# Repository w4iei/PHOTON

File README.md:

# PHOTON
**PHysical Optical Tracking of Notes system**

PHOTON is a modular, open-source optical sensing platform for high-resolution key and motion tracking. Each module combines a KiCad-designed linear array of **VCNT2025X01** reflective sensors, **TLA2518** high-speed SPI ADCs, and an **RP2350** MCU. Modules can run standalone over USB-C or daisy-chain over RS-485 for large sensing surfaces.

## Paper
[PHOTON: Non-Invasive Optical Tracking of Key-Lever Motion in Historical Keyboard Instruments](https://arxiv.org/abs/2604.21682) (arXiv:2604.21682)

## Demo

[Watch the PHOTON demo playlist on YouTube](https://www.youtube.com/playlist?list=PLzCRAfVYuoWGEnWNO6l8IuFvaSUI3v1Gd)

## Highlights
- **Sensors:** [VCNT2025X01](https://www.vishay.com/en/product/84895/) reflective array with per-sensor enable lines
- **Digitization:** [TLA2518](https://www.ti.com/product/TLA2518) SPI ADCs for high-speed readout
- **MCU:** [RP2350](https://www.raspberrypi.com/products/rp2350/) (dual-core Cortex-M33)
- **Comms:** [THVD1424](https://www.ti.com/product/THVD1424) RS-485 transceivers; firmware-controlled termination on the main board (idle-bus failsafe via the transceiver's internal receiver thresholds on this hardware rev)
- **I/O:** USB-C (power + USB-MIDI/CDC), QWIIC/I2C expansion
- **Black box:** a microSD card in the bridge records every performance as Standard MIDI Files, host or no host (see [firmware/README.md](firmware/README.md#microsd-recorder-bridge))
- **Open:** KiCad 9 hardware, native C firmware (Pico SDK)

## Performance
- Full 31-sensor board sweep in ~770 µs — ~1.3 kHz open-loop; production runs two-phase, pace-throttled at 600 Hz (half the peak emitter current, 1.67 ms velocity quantisation) with µs-resolution velocity timing either way
- RS-485 bus at 4 Mbaud, bridge-polled: zero collisions by construction, zero event loss across ~500k sequence-accounted bench events, sub-ms worst-case event latency with four boards on the bus

## Firmware (native C, dual-core)
CircuitPython support is gone: it capped the system at a ~250 Hz single-core scan loop and could not prevent bus collisions, so it was retired for performance. The native Pico-SDK firmware ships as **one UF2 for every board** — each board probes its own hardware at boot and becomes a sensor node or the main bridge automatically:
- **Core 1** owns the sensor array: pipelined TLA2518 scanning, running entirely from SRAM so flash and USB activity can never stall a sweep.
- **Core 0** owns everything else: USB (CDC console + USB-MIDI), the RS-485 protocol, calibration and configuration storage.
- **RS-485:** one board is the sole bus master — the main board, or with `master on` the sensor board that carries the USB cable — and polls each sensor board in turn; nodes never transmit unsolicited, and every event batch is acknowledged before a node releases it — collision-free and lossless by design.
- **Scanning:** free-runs open-loop at ~1.3 kHz; throttled to a paced 600 Hz (two-phase mode) for production use.
- **microSD recorder:** a card in the bridge records every performance automatically as Standard MIDI Files, numbered per power-on and per playing episode, with no host, no setup and no clock required.

Build and flash instructions: `firmware/README.md`.

## Architecture (Short)
- Sensor boards: VCNT2025X01 array -> TLA2518 SPI ADCs -> RP2350
- Main board: RP2350 + THVD1424 RS-485 + bias resistors + termination control
- Bus: RS-485 differential, terminated at endpoints

## Hardware
See `hardware/README.md` for board-specific notes and layout sources.

## Getting Started
**Hardware**
- PHOTON module(s)
- USB-C cable
- JST-SH 4-pin cables (1.0 mm pitch, "reverse double head" type as used by Qwiic; see `hardware/README.md`)
- Mounting screws: **M2.3 x 5 mm pan head**, through the boards' 2.7 mm (M2.5) holes; at least three per board over 250 mm long, one at each end and one near the middle (see [hardware/README.md](hardware/README.md#design-recommendations))

**Software**
- PHOTON firmware UF2 (build from `firmware/`, see `firmware/README.md`)
- KiCad 9 (download: https://www.kicad.org/download/)
- DAW or MIDI viewer (Pianoteq, Ableton Live, Reaper, Max/MSP, etc.)

## Build & Flash
1. A new board arrives with empty flash, so it comes up in BOOTSEL on its own: connect via USB-C and copy `photon.uf2` to the mounted `RP2350` drive. The same image runs every board.
2. On each sensor board, set its bus id once via the USB console (`setid N`); in an instrument without a main board, also `master on` on each (see `firmware/README.md`).
3. Calibrate. Two ways:
   - **One board, on its own USB console:** `r` clears that board's table and starts learning; play every key it covers once, one at a time, with a normal full stroke; `s` freezes the table and saves it (`x` aborts without saving).
   - **The whole instrument, from the bridge console:** `cal reset` clears every sensor board and starts learning on all of them; play every key on every manual; `cal save` then stores each board's table in its own flash. To redo a single board without disturbing the others, give its bus id: `cal reset <id>`, play that board's keys, `cal save <id>`.

   Calibration and configuration persist in flash and survive reflashing; only `cal reset`, `r` and `setid` clear them.
4. Boards already running PHOTON reflash over USB alone: the `bootsel` console command re-enters the bootloader, so the `RP2350` drive comes back without touching the board. **USB-BOOT** (hold while connecting USB-C, or short the jumper) is only needed to recover a board whose console is unreachable.

## Notes
- **Double-manual harpsichords** run on a single bus: each manual is a pair of sensor boards mapped to its own MIDI channel (`chmap` console command). The polled protocol eliminates inter-board collisions, so simultaneous playing on both manuals loses nothing.

## Citation
```bibtex
@inproceedings{photon2026,
  title       = {PHOTON: Non-Invasive Optical Tracking of Key-Lever Motion in Historical Keyboard Instruments},
  author      = {Noah Jaffe and John Ashley Burgoyne},
  booktitle   = {Proceedings of the 2026 International Conference on New Interfaces for Musical Expression (NIME)},
  year        = {2026},
  address     = {London, UK},
  note        = {23--26 June 2026. Preprint: arXiv:2604.21682},
  url         = {https://arxiv.org/abs/2604.21682},
}
```

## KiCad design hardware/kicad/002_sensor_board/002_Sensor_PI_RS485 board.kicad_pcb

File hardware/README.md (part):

## Hardware Overview

KiCad sources for the PHOTON boards. Three designs, all sharing one symbol
library (`PHOTON.kicad_sym`, `PHOTON_Modified.kicad_sym`) and one footprint
library (`photon_common.pretty`) at the top of `hardware/kicad/`.

| Board | Size | Role |
|---|---|---|
| `002_sensor_board` | 413.7 x 35.0 mm | Sensor node — 31 optical sensors |
| `001d_..._low_profile` | 54.0 x 41.7 mm | Bridge, low cost / low profile |
| `001_main_controller_board` | 69.0 x 49.9 mm | Bridge, full size, touchscreen |

### Datasheets

- [VCNT2025X01](https://www.vishay.com/docs/84895/vcnt2025x01.pdf) — reflective optical sensor (Vishay)
- [TLA2518](https://www.ti.com/lit/ds/symlink/tla2518.pdf) — 8-channel SPI ADC (TI)
- [RP2350 / RP2354](https://datasheets.raspberrypi.com/rp2350/rp2350-datasheet.pdf) — microcontroller (Raspberry Pi); the RP2354 is the RP2350 with 2 MB of flash in the package, same datasheet
- [THVD1424](https://www.ti.com/lit/ds/symlink/thvd1424.pdf) — RS-485 transceiver (TI)
- [TPS62A0569A](https://www.ti.com/lit/gpn/tps62a0569a) — buck regulator (TI)
- [Waveshare 2.8" capacitive touch LCD](https://www.waveshare.com/wiki/2.8inch_Capacitive_Touch_LCD) — ST7789T3 display controller, CST328 touch controller; the reference panel for the 001 bridge

## 002 — Sensor node

31 VCNT2025X01 reflective sensors on a **13.3 mm pitch**, read by eight
TLA2518 8-channel ADCs, scanned by an RP2354. One board covers 31 notes, so
**two boards cover a 56-62 key manual** and four cover a double-manual
instrument.

This example is dimensioned for 13.3 mm, measured at either sensing point —
under the **jack** or under the **key lever**. **Every harpsichord is
different.** Measure your own instrument and validate the fit before ordering
boards.

Smaller compasses (58 keys GG–e‴, for example) often have no centre vertical
rail, so the boards mount on the horizontal rail near the pins at the far end
of the keybed; check the clearance there carefully. Many instruments taper,
so the jack spacing is not 13.33 mm: either make a board to match, or mount
the standard board where the keys' centre-to-centre spacing is 13.33 mm.

**The board is designed to be shortened.** Mousebite perforations
(`photon_common:mousebite_34mm`) let you snap or cut sections off with
scissors to fit a shorter compass or an awkward case. Signals are routed
*through* the mousebite regions — sensor enables, ADC inputs, VCC and GND —
so a cut section stays functional up to the break.

## 001D — Bridge, low profile

RP2354 (2 MB internal flash), USB-C to the host, THVD1424 to the sensor bus,
microSD. Minimal part count and the smallest board that does the job. This is
the default bridge.

## 001 — Bridge, full size

Same role, plus an **18-pin 0.5 mm FPC connector (FH34SRJ-18S-0.5SH)** for a
touchscreen — the reference panel is a Waveshare 2.8" 240x320, ST7789T3 over
SPI with a CST328 capacitive touch controller over I2C. Carries RP2350 with
external W25Q128 flash and an APS6404L PSRAM, plus one VCNT2025X01 fitted for
bench work. Use this only if the application wants a local display.

### Touchscreen and PSRAM bring-up notes

Verified on 2026-09-30 on an early 001 ("A003"). Its pins match every
schematic revision:

| Signal | GPIO |
|---|---|
| LCD SPI1 SCK / MOSI / MISO | 10 / 11 / 12 (shared with the microSD socket) |
| LCD CS / DC / RST / backlight | 8 / 14 / 9 / 15 |
| Touch I2C1 SDA / SCL | 6 / 7 |
| Touch INT / RST | 2 / 3 |
| PSRAM CS (QMI CS1) | 0 |

- **Display.** The ST7789T3 runs at 37.5 MHz SPI (clk_peri / 4), with colour
  order RGB and inversion on. It **never answers register reads** on this
  board: MISO and SDA both read the microSD socket's pull-ups. So check first
  light by eye, not by reading an ID.
- **Touch.** The CST328 (address 0x1A, signature 0xCACA, reports 240x320)
  sends a report every ~26 ms while a finger is down. **INT falls about 2 ms
  before the report registers are updated.** Read the chip right on the edge
  and you get the previous, already-consumed report, which says zero
  fingers. So wait ~2 ms after INT, and treat a finger as lifted only after
  ~80 ms without a report. The observed worst gap was 72 ms. A shorter window
  releases and re-presses a held finger, and that double-toggles buttons.
- **PSRAM.** The APS6404L answers on GPIO0 (known-good-die byte 0x5D, 8 MB). A full
  8 MB write/read test passed with 0 errors.

Firmware support lives in `firmware/src/hw/psram.c` (board support; the
PHOTON image doesn't call it). The **optional** touchscreen drivers are in
`firmware/src/touchscreen/`. They are only for firmware that wants a local
UI, and are built only with `-DPHOTON_TOUCHSCREEN=ON`, which fetches LVGL.

## No bridge at all

**Neither bridge board is required.** A sensor node has its own USB-C
receptacle, so running a USB-C cable from one sensor board straight to the
host is a complete system. Several sensor boards work the same way once each
has `master on` saved: the board carrying the USB cable runs the bus for the
others (see
[firmware/README.md](../firmware/README.md#without-a-main-controller-board)).
The bridge exists for installations that want the host connection somewhere
other than at a sensor board, or that want a touchscreen and the microSD
recorder.

In practice a bridge is often the easier build. Once the sensor boards are
mounted under the keys or jacks, their USB-C receptacles tend to end up
somewhere a USB-C plug cannot reach or cannot exit the case from. The
inter-board lead is a thin 4-pin JST-SH cable that bends around anything, so
the bridge — and with it the USB-C socket and the microSD slot — can sit
wherever the host connection is convenient. The cable type is specified under
[Power](#power).

## Power

**The RS-485 cable carries 5 V.** Every board — sensor node and bridge alike —
regulates its own 3.3 V locally with a TPS62A0569ADRLR buck. Nets are just
`+5V` and `+3V3`; there is no shared 3.3 V rail between boards.

Inter-board cable, 4-pin JST-SH:

| Pin | Net |
|---|---|
| 1 | GND |
| 2 | +5V |
| 3 | RS485_P |
| 4 | RS485_N |

Use a 4-pin JST-SH (1.0 mm pitch) **"reverse double head"** cable — the same
lead Qwiic uses. Check it before plugging in: hold both plugs facing you in
the same orientation and the top-left wire colour must be the same on both.
[Example listing](https://nl.aliexpress.com/item/1005011775162638.html).

Feedback divider is 0.6 V x (1 + 450k/100k) = 3.3 V.

### One host at a time

Every board's USB-C VBUS sits on the same `+5V` net as its RS-485 connectors,
so the whole chain shares one 5 V rail. Powering any single board over USB
powers every board on the bus — which is what makes an instrument without a
main controller board work (`master on` on every sensor board; the one with
the USB cable runs the bus, see
[firmware/README.md](../firmware/README.md#without-a-main-controller-board)).

**Do not plug two boards into two different computers at once.** That ties both
hosts' 5 V supplies together through the cable. One USB connection to the
system at a time.

### Budget

The whole four-board system draws **~210 mA at 5 V (1.08 W)** while
scanning at the production settings, i.e. roughly 60 mA at 3.3 V per board:
the RP2350 at 150 MHz and eight always-on TLA2518s. Emitters are pulsed at a
few percent duty and cost ~0.1 W per 100 Hz of scan rate; peak current
depends on scan mode (up to four lit at once in two-phase, ~27 mA each, or
eight in parallel).

COUT is **22 uF**, the value the TPS62A0569A datasheet rates highest with a
1 uH inductor. Do not add distributed bulk on +3V3 to "help" — it parallels
COUT and slows the loop, which costs more than the droop it removes.

### Rail sensitivity

The detector is a 4.7 kOhm pull-up to +3V3 with the ADC referenced to the same
rail, so the dark reading is ratiometric and only the LED's forward-voltage
offset leaks through: **~1.9% of signal per 100 mV of droop**, about 130 counts
on a 6,900-count range against a ~62-count noise floor. Keep emitter-correlated
droop under ~50 mV and it is invisible.

Do not filter AVDD away from the pull-up rail — that breaks the cancellation
and roughly triples the sensitivity.

## Building a sensor board for your instrument

1. Update the schematic so the sensor and bank counts match your instrument.
   The final sensor bank is **not** inherited from the four-sensor bank — edit
   it explicitly.
2. Resize the board outline, copper fills and edge cuts.
3. Run the sensor placement script to set the pitch.
4. Route the first bank and the last bank.
5. Replicate that routing across the middle banks, then clean up and verify by
   hand.

Manual review is required after replication and before fabrication.

## Required KiCad plugins

Both via the Plugin and Content Manager:

- **Replicate Layout** — step 5 above
- **Fabrication Toolkit** — generates the `production/` outputs

## Design recommendations

For a board over 250 mm long, use at least **three M2.5 mounting holes** — one at each
end and one near the middle. The centre screw stops the board bowing away from
the mounting surface. Fit them in a line, not both ends first. Putty is fine
for a temporary setup; screws keep the boards from shifting when the
instrument is moved.

Mounting holes use `photon_common:MountingHole_2.7mm_M2.5_Keepout`, which
carries a 7 mm copper keepout so a screw head cannot bridge the top pour to
the bottom pour.

Recommended screws: **M2.3 x 5 mm pan head**
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
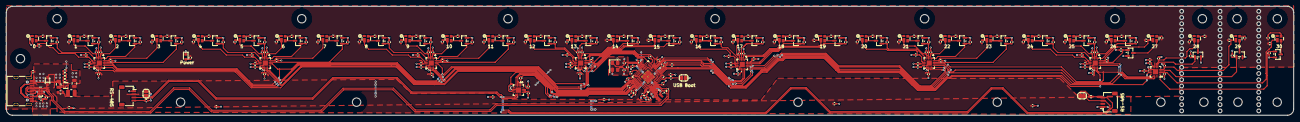
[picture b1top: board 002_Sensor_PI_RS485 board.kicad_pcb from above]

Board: 2 copper layers, 413.7 x 35.0 mm, 300 parts (0 on the bottom side), 183 nets.

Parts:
C1: 4.7uF; C_0805_2012Metric
C2, C3: 4.7uF; C_0402_1005Metric_small_pads
C4: 22uF; C_0805_2012Metric
C5, C8, C9, C13, C14, C15, C16, C19, C20, C21, C22, C23, C24, C25, C26, C27: 100nF; C_0402_1005Metric
C6, C7: 4.7uF; C_0402_1005Metric
C10, C401, C402, C403, C801, C802, C803, C1301, C1302, C1303, C1801, C1802, C1803, C2301, C2302, C2303, C2801, C2802, C2803, C3301, C3302, C3303, C3801, C3802, C3803: 1uF; C_0402_1005Metric
C17, C18: 15pF; C_0402_1005Metric
C404, C405, C406, C407, C804, C805, C806, C807, C1304, C1305, C1306, C1307, C1804, C1805, C1806, C1807, C2304, C2305, C2306, C2307, C2804, C2805, C2806, C2807, C3304, C3305, C3306, C3307, C3804, C3805, C3806: 1nF; C_0402_1005Metric
CR1: PTVSHC3D7VU; SOD-323_L1.8-W1.3-LS2.5-RD
D3: LED RED; LED_0603_1608Metric
FB1: FerriteBead; L_0603_1608Metric
H1, H2, H3, H4, H5, H6, H7, H8, H9, H10, H11, H12, H13, H14, H15, H16, H17, H18: MountingHole; MountingHole_2.7mm_M2.5_Keepout
H3801, H3802, H3803: Mousebites to detatch sensor; mousebite_34mm
J1, J2: JST_SH; JST_SH_SM04B-SRSS-TB_1x04-1MP_P1.00mm_Horizontal
J3: USB_C_Receptacle_USB2.0; USB_C_Receptacle_HRO_TYPE-C-31-M-12
JP1, JP2, JP4: SolderJumper_2_Open; SolderJumper-2_P1.3mm_Open_RoundedPad1.0x1.5mm
L1: 3.3uH; L_pol_2016
L2: 1uH; L_1008_2520Metric
Q301, Q501, Q601, Q701, Q901, Q1001, Q1101, Q1201, Q1401, Q1501, Q1601, Q1701, Q1901, Q2001, Q2101, Q2201, Q2401, Q2501, Q2601, Q2701, Q2901, Q3001, Q3101, Q3201, Q3401, Q3501, Q3601, Q3701, Q4301, Q4401, Q4501: AO3400A; SOT-23
R1: 0Ω; R_0402_1005Metric
R2, R3: 5.1kΩ; R_0402_1005Metric
R4, R5: 120Ω; R_0402_1005Metric
R6, R11, R12: 33Ω; R_0402_1005Metric
R7, R18: 1kΩ; R_0402_1005Metric
R8, R102: 10kΩ; R_0402_1005Metric
R13, R14, R19, R20: 22Ω; R_0402_1005Metric
R103, R301, R501, R601, R701, R901, R1001, R1101, R1201, R1401, R1501, R1601, R1701, R1901, R2001, R2101, R2201, R2401, R2501, R2601, R2701, R2901, R3001, R3101, R3201, R3401, R3501, R3601, R3701, R4301, R4401, R4501: 100kΩ; R_0402_1005Metric
R104, R105: 200kΩ; R_0402_1005Metric
R106: 51kΩ; R_0402_1005Metric
R302, R502, R602, R702, R902, R1002, R1102, R1202, R1402, R1502, R1602, R1702, R1902, R2002, R2102, R2202, R2402, R2502, R2602, R2702, R2902, R3002, R3102, R3202, R3402, R3502, R3602, R3702, R4302, R4402, R4502: 68Ω; R_0402_1005Metric
R303, R503, R603, R703, R903, R1003, R1103, R1203, R1403, R1503, R1603, R1703, R1903, R2003, R2103, R2203, R2403, R2503, R2603, R2703, R2903, R3003, R3103, R3203, R3403, R3503, R3603, R3703, R4303, R4403, R4503: 4.7kΩ; R_0402_1005Metric
U1: RP2354_60QFN; RP2350-QFN-60-1EP_7x7_P0.4mm_EP3.4x3.4mm_ThermalVias
U4: TPD4E05U06DQAR; DQA0010A
U5: THVD1424RGTR; QFN_24RGTR_TEX
U6: TPS62A0569ADRLR; SOT-563_DRL0006A
U301, U501, U601, U701, U901, U1001, U1101, U1201, U1401, U1501, U1601, U1701, U1901, U2001, U2101, U2201, U2401, U2501, U2601, U2701, U2901, U3001, U3101, U3201, U3401, U3501, U3601, U3701, U4301, U4401, U4501: VCNT2025X01; VCNT2025X01_VIS
U401, U801, U1301, U1801, U2301, U2801, U3301, U3801: TLA2518IRTER; WQFN16_RTE_TEX
Y1: ABM8-272-T3; Crystal_SMD_3225-4Pin_3.2x2.5mm

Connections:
+1V1: C3.1, C5.1, C7.1, C8.1, L1.1, U1.6 (DVDD), U1.23 (DVDD), U1.39 (DVDD), U1.50 (VREG_FB)
+3V3: C2.1, C4.1, C9.1, C10.1, C13.1, C14.1, C15.1, C16.1, C19.1, C20.1, C21.1, C401.1, C403.1, C801.1, C803.1, C1301.1, C1303.1, C1801.1, C1803.1, C2301.1, C2303.1, C2801.1, C2803.1, C3301.1, C3303.1, C3801.1, C3803.1, L2.2, R6.1, R8.2, R102.2, R104.2, R302.1, R303.1, R502.1, R503.1, R602.1, R603.1, R702.1, R703.1, R902.1, R903.1, R1002.1, R1003.1, R1102.1, R1103.1, R1202.1, R1203.1, R1402.1, R1403.1, R1502.1, R1503.1, R1602.1, R1603.1, R1702.1, R1703.1, R1902.1, R1903.1, R2002.1, R2003.1, R2102.1, R2103.1, R2202.1, R2203.1, R2402.1, R2403.1, R2502.1, R2503.1, R2602.1, R2603.1, R2702.1, R2703.1, R2902.1, R2903.1, R3002.1, R3003.1, R3102.1, R3103.1, R3202.1, R3203.1, R3402.1, R3403.1, R3502.1, R3503.1, R3602.1, R3603.1, R3702.1, R3703.1, R4302.1, R4303.1, R4402.1, R4403.1, R4502.1, R4503.1, U1.1 (IOVDD), U1.11 (IOVDD), U1.20 (IOVDD), U1.30 (IOVDD), U1.38 (IOVDD), U1.44 (ADC_AVDD), U1.45 (IOVDD), U1.49 (VREG_VIN), U1.53 (USB_OTP_VDD), U1.54 (QSPI_IOVDD), U5.13 (VIO), U5.14 (VCC), U5.15 (H/F), U401.7 (AVDD), U401.10 (DVDD), U801.7 (AVDD), U801.10 (DVDD), U1301.7 (AVDD), U1301.10 (DVDD), U1801.7 (AVDD), U1801.10 (DVDD), U2301.7 (AVDD), U2301.10 (DVDD), U2801.7 (AVDD), U2801.10 (DVDD), U3301.7 (AVDD), U3301.10 (DVDD), U3801.7 (AVDD), U3801.10 (DVDD)
+5V: C22.1, C23.1, C24.1, C25.1, C26.1, C27.1, CR1.1 (K), FB1.1, J1.2, J2.2, J3.A4 (VBUS), J3.A9 (VBUS), J3.B4 (VBUS), J3.B9 (VBUS)
/BANK_0_CS: U1.33 (GPIO21), U401.11 (*CS)
/BANK_1_CS: U1.32 (GPIO20), U801.11 (*CS)
/BANK_2_CS: U1.31 (GPIO19), U1301.11 (*CS)
/BANK_3_CS: U1.19 (GPIO15), U1801.11 (*CS)
/BANK_4_CS: U1.3 (GPIO1), U2301.11 (*CS)
/BANK_5_CS: U1.10 (GPIO7), U2801.11 (*CS)
/BANK_6_CS: U1.8 (GPIO5), U3301.11 (*CS)
/BANK_7_CS: U1.9 (GPIO6), U3801.11 (*CS)
/GPIO0: U1.2 (GPIO0), U2301.12 (SDO), U2801.12 (SDO), U3301.12 (SDO), U3801.12 (SDO)
/GPIO2: R14.2, U1.4 (GPIO2)
/GPIO3: U1.5 (GPIO3), U2301.14 (SDI), U2801.14 (SDI), U3301.14 (SDI), U3801.14 (SDI)
/GPIO8: U1.12 (GPIO8), U401.12 (SDO), U801.12 (SDO), U1301.12 (SDO), U1801.12 (SDO)
/GPIO10: R13.2, U1.14 (GPIO10)
/GPIO11: U1.15 (GPIO11), U401.14 (SDI), U801.14 (SDI), U1301.14 (SDI), U1801.14 (SDI)
/GPIO22: R19.2, U1.34 (GPIO22)
/GPIO23: R20.2, U1.35 (GPIO23)
/GPIO24: U1.36 (GPIO24), U5.2 (RE), U5.3 (DE)
/GPIO25: U1.37 (GPIO25), U5.5 (TERM_TX), U5.7 (TERM_RX)
/QSPI_SS: R7.1, U1.60 (QSPI_SS)
/RS485_N: J1.4, J2.4, R4.2, R5.2, U5.10 (Z)
/RS485_P: J1.3, J2.3, JP1.1 (A), JP2.1 (A), U5.9 (Y)
/RUN: R102.1, U1.26 (RUN)
/SPI0_SCLK: R13.1, U401.13 (SCLK), U801.13 (SCLK), U1301.13 (SCLK), U1801.13 (SCLK)
/SPI1_SCLK: R14.1, U2301.13 (SCLK), U2801.13 (SCLK), U3301.13 (SCLK), U3801.13 (SCLK)
/Sensor Array/4_Sensor_bank1/EN0: Q901.1 (G), R901.1, U801.5 (AIN6/GPIO6)
/Sensor Array/4_Sensor_bank1/EN1: Q1001.1 (G), R1001.1, U801.3 (AIN4/GPIO4)
/Sensor Array/4_Sensor_bank1/EN2: Q1101.1 (G), R1101.1, U801.1 (AIN2/GPIO2)
/Sensor Array/4_Sensor_bank1/EN3: Q1201.1 (G), R1201.1, U801.15 (AIN0/GPIO0)
/Sensor Array/4_Sensor_bank1/Y0: C804.1, R903.2, U801.6 (AIN7/GPIO7), U901.2
/Sensor Array/4_Sensor_bank1/Y1: C805.1, R1003.2, U801.4 (AIN5/GPIO5), U1001.2
/Sensor Array/4_Sensor_bank1/Y2: C806.1, R1103.2, U801.2 (AIN3/GPIO3), U1101.2
/Sensor Array/4_Sensor_bank1/Y3: C807.1, R1203.2, U801.16 (AIN1/GPIO1), U1201.2
/Sensor Array/4_Sensor_bank2/EN0: Q1401.1 (G), R1401.1, U1301.5 (AIN6/GPIO6)
/Sensor Array/4_Sensor_bank2/EN1: Q1501.1 (G), R1501.1, U1301.3 (AIN4/GPIO4)
/Sensor Array/4_Sensor_bank2/EN2: Q1601.1 (G), R1601.1, U1301.1 (AIN2/GPIO2)
/Sensor Array/4_Sensor_bank2/EN3: Q1701.1 (G), R1701.1, U1301.15 (AIN0/GPIO0)
/Sensor Array/4_Sensor_bank2/Y0: C1304.1, R1403.2, U1301.6 (AIN7/GPIO7), U1401.2
/Sensor Array/4_Sensor_bank2/Y1: C1305.1, R1503.2, U1301.4 (AIN5/GPIO5), U1501.2
/Sensor Array/4_Sensor_bank2/Y2: C1306.1, R1603.2, U1301.2 (AIN3/GPIO3), U1601.2
/Sensor Array/4_Sensor_bank2/Y3: C1307.1, R1703.2, U1301.16 (AIN1/GPIO1), U1701.2
/Sensor Array/4_Sensor_bank3/EN0: Q1901.1 (G), R1901.1, U1801.5 (AIN6/GPIO6)
/Sensor Array/4_Sensor_bank3/EN1: Q2001.1 (G), R2001.1, U1801.3 (AIN4/GPIO4)
/Sensor Array/4_Sensor_bank3/EN2: Q2101.1 (G), R2101.1, U1801.1 (AIN2/GPIO2)
/Sensor Array/4_Sensor_bank3/EN3: Q2201.1 (G), R2201.1, U1801.15 (AIN0/GPIO0)
/Sensor Array/4_Sensor_bank3/Y0: C1804.1, R1903.2, U1801.6 (AIN7/GPIO7), U1901.2
/Sensor Array/4_Sensor_bank3/Y1: C1805.1, R2003.2, U1801.4 (AIN5/GPIO5), U2001.2
/Sensor Array/4_Sensor_bank3/Y2: C1806.1, R2103.2, U1801.2 (AIN3/GPIO3), U2101.2
/Sensor Array/4_Sensor_bank3/Y3: C1807.1, R2203.2, U1801.16 (AIN1/GPIO1), U2201.2
/Sensor Array/4_Sensor_bank4/EN0: Q2401.1 (G), R2401.1, U2301.5 (AIN6/GPIO6)
/Sensor Array/4_Sensor_bank4/EN1: Q2501.1 (G), R2501.1, U2301.3 (AIN4/GPIO4)
/Sensor Array/4_Sensor_bank4/EN2: Q2601.1 (G), R2601.1, U2301.1 (AIN2/GPIO2)
/Sensor Array/4_Sensor_bank4/EN3: Q2701.1 (G), R2701.1, U2301.15 (AIN0/GPIO0)
/Sensor Array/4_Sensor_bank4/Y0: C2304.1, R2403.2, U2301.6 (AIN7/GPIO7), U2401.2
/Sensor Array/4_Sensor_bank4/Y1: C2305.1, R2503.2, U2301.4 (AIN5/GPIO5), U2501.2
/Sensor Array/4_Sensor_bank4/Y2: C2306.1, R2603.2, U2301.2 (AIN3/GPIO3), U2601.2
/Sensor Array/4_Sensor_bank4/Y3: C2307.1, R2703.2, U2301.16 (AIN1/GPIO1), U2701.2
/Sensor Array/4_Sensor_bank5/EN0: Q2901.1 (G), R2901.1, U2801.5 (AIN6/GPIO6)
/Sensor Array/4_Sensor_bank5/EN1: Q3001.1 (G), R3001.1, U2801.3 (AIN4/GPIO4)
/Sensor Array/4_Sensor_bank5/EN2: Q3101.1 (G), R3101.1, U2801.1 (AIN2/GPIO2)
/Sensor Array/4_Sensor_bank5/EN3: Q3201.1 (G), R3201.1, U2801.15 (AIN0/GPIO0)
/Sensor Array/4_Sensor_bank5/Y0: C2804.1, R2903.2, U2801.6 (AIN7/GPIO7), U2901.2
/Sensor Array/4_Sensor_bank5/Y1: C2805.1, R3003.2, U2801.4 (AIN5/GPIO5), U3001.2
/Sensor Array/4_Sensor_bank5/Y2: C2806.1, R3103.2, U2801.2 (AIN3/GPIO3), U3101.2
/Sensor Array/4_Sensor_bank5/Y3: C2807.1, R3203.2, U2801.16 (AIN1/GPIO1), U3201.2
/Sensor Array/4_Sensor_bank6/EN0: Q3401.1 (G), R3401.1, U3301.5 (AIN6/GPIO6)
/Sensor Array/4_Sensor_bank6/EN1: Q3501.1 (G), R3501.1, U3301.3 (AIN4/GPIO4)
/Sensor Array/4_Sensor_bank6/EN2: Q3601.1 (G), R3601.1, U3301.1 (AIN2/GPIO2)
/Sensor Array/4_Sensor_bank6/EN3: Q3701.1 (G), R3701.1, U3301.15 (AIN0/GPIO0)
/Sensor Array/4_Sensor_bank6/Y0: C3304.1, R3403.2, U3301.6 (AIN7/GPIO7), U3401.2
/Sensor Array/4_Sensor_bank6/Y1: C3305.1, R3503.2, U3301.4 (AIN5/GPIO5), U3501.2
/Sensor Array/4_Sensor_bank6/Y2: C3306.1, R3603.2, U3301.2 (AIN3/GPIO3), U3601.2
/Sensor Array/4_Sensor_bank6/Y3: C3307.1, R3703.2, U3301.16 (AIN1/GPIO1), U3701.2
/Sensor Array/4_Sensor_bank/EN0: Q301.1 (G), R301.1, U401.5 (AIN6/GPIO6)
/Sensor Array/4_Sensor_bank/EN1: Q501.1 (G), R501.1, U401.3 (AIN4/GPIO4)
/Sensor Array/4_Sensor_bank/EN2: Q601.1 (G), R601.1, U401.1 (AIN2/GPIO2)
/Sensor Array/4_Sensor_bank/EN3: Q701.1 (G), R701.1, U401.15 (AIN0/GPIO0)
/Sensor Array/4_Sensor_bank/Y0: C404.1, R303.2, U301.2, U401.6 (AIN7/GPIO7)
/Sensor Array/4_Sensor_bank/Y1: C405.1, R503.2, U401.4 (AIN5/GPIO5), U501.2
/Sensor Array/4_Sensor_bank/Y2: C406.1, R603.2, U401.2 (AIN3/GPIO3), U601.2
/Sensor Array/4_Sensor_bank/Y3: C407.1, R703.2, U401.16 (AIN1/GPIO1), U701.2
/Sensor Array/Last_sensor_bank/EN0: Q4301.1 (G), R4301.1, U3801.5 (AIN6/GPIO6)
/Sensor Array/Last_sensor_bank/EN1: Q4401.1 (G), R4401.1, U3801.3 (AIN4/GPIO4)
/Sensor Array/Last_sensor_bank/EN2: Q4501.1 (G), R4501.1, U3801.1 (AIN2/GPIO2)
/Sensor Array/Last_sensor_bank/Y0: C3804.1, R4303.2, U3801.6 (AIN7/GPIO7), U4301.2
/Sensor Array/Last_sensor_bank/Y1: C3805.1, R4403.2, U3801.4 (AIN5/GPIO5), U4401.2
/Sensor Array/Last_sensor_bank/Y2: C3806.1, R4503.2, U3801.2 (AIN3/GPIO3), U4501.2
/UART_RX: R20.1, U5.1 (R)
/UART_TX: R19.1, U5.4 (D)
/USB_D+: J3.A6 (D+), J3.B6 (D+), R11.1, U4.4 (D2+), U4.7 (NC)
/USB_D-: J3.A7 (D-), J3.B7 (D-), R12.1, U4.5 (D2-), U4.6 (NC)
/VREG_AVDD: C6.1, R6.2, U1.46 (VREG_AVDD)
/VREG_LX: L1.2, U1.48 (VREG_LX)
/XIN: C17.1, U1.21 (XIN), Y1.1
/XOUT: R18.1, U1.22 (XOUT)
/~USB_BOOT: JP4.2 (B), R7.2
GND: C1.2, C2.2, C3.2, C4.2, C5.2, C6.2, C7.2, C8.2, C9.2, C10.2, C13.2, C14.2, C15.2, C16.2, C17.2, C18.2, C19.2, C20.2, C21.2, C22.2, C23.2, C24.2, C25.2, C26.2, C27.2, C401.2, C402.2, C403.2, C404.2, C405.2, C406.2, C407.2, C801.2, C802.2, C803.2, C804.2, C805.2, C806.2, C807.2, C1301.2, C1302.2, C1303.2, C1304.2, C1305.2, C1306.2, C1307.2, C1801.2, C1802.2, C1803.2, C1804.2, C1805.2, C1806.2, C1807.2, C2301.2, C2302.2, C2303.2, C2304.2, C2305.2, C2306.2, C2307.2, C2801.2, C2802.2, C2803.2, C2804.2, C2805.2, C2806.2, C2807.2, C3301.2, C3302.2, C3303.2, C3304.2, C3305.2, C3306.2, C3307.2, C3801.2, C3802.2, C3803.2, C3804.2, C3805.2, C3806.2, CR1.2 (A), D3.1 (K), J1.1, J2.1, J3.A1 (GND), J3.A12 (GND), J3.B1 (GND), J3.B12 (GND), JP4.1 (A), Q301.2 (S), Q501.2 (S), Q601.2 (S), Q701.2 (S), Q901.2 (S), Q1001.2 (S), Q1101.2 (S), Q1201.2 (S), Q1401.2 (S), Q1501.2 (S), Q1601.2 (S), Q1701.2 (S), Q1901.2 (S), Q2001.2 (S), Q2101.2 (S), Q2201.2 (S), Q2401.2 (S), Q2501.2 (S), Q2601.2 (S), Q2701.2 (S), Q2901.2 (S), Q3001.2 (S), Q3101.2 (S), Q3201.2 (S), Q3401.2 (S), Q3501.2 (S), Q3601.2 (S), Q3701.2 (S), Q4301.2 (S), Q4401.2 (S), Q4501.2 (S), R1.2, R2.1, R3.1, R103.2, R301.2, R501.2, R601.2, R701.2, R901.2, R1001.2, R1101.2, R1201.2, R1401.2, R1501.2, R1601.2, R1701.2, R1901.2, R2001.2, R2101.2, R2201.2, R2401.2, R2501.2, R2601.2, R2701.2, R2901.2, R3001.2, R3101.2, R3201.2, R3401.2, R3501.2, R3601.2, R3701.2, R4301.2, R4401.2, R4501.2, U1.47 (VREG_PGND), U1.61 (GND), U4.3 (GND), U4.8 (GND), U5.6 (GND), U5.17 (GND), U6.2 (GND), U301.1, U401.9 (GND), U401.17 (GND), U501.1, U601.1, U701.1, U801.9 (GND), U801.17 (GND), U901.1, U1001.1, U1101.1, U1201.1, U1301.9 (GND), U1301.17 (GND), U1401.1, U1501.1, U1601.1, U1701.1, U1801.9 (GND), U1801.17 (GND), U1901.1, U2001.1, U2101.1, U2201.1, U2301.9 (GND), U2301.17 (GND), U2401.1, U2501.1, U2601.1, U2701.1, U2801.9 (GND), U2801.17 (GND), U2901.1, U3001.1, U3101.1, U3201.1, U3301.9 (GND), U3301.17 (GND), U3401.1, U3501.1, U3601.1, U3701.1, U3801.9 (GND), U3801.17 (GND), U4301.1, U4401.1, U4501.1, Y1.2, Y1.4
unnamed: C18.1, R18.2, Y1.3
unnamed: D3.2 (A), R8.1
unnamed: J3.A5 (CC1), R2.2, U4.1 (D1+), U4.10 (NC)
unnamed: J3.B5 (CC2), R3.2, U4.2 (D1-), U4.9 (NC)
unnamed: J3.SH (SHIELD), R1.1
unnamed: JP1.2 (B), R4.1
unnamed: JP2.2 (B), R5.1
unnamed: Q301.3 (D), U301.4 (K)
unnamed: Q501.3 (D), U501.4 (K)
unnamed: Q601.3 (D), U601.4 (K)
unnamed: Q701.3 (D), U701.4 (K)
unnamed: Q901.3 (D), U901.4 (K)
unnamed: Q1001.3 (D), U1001.4 (K)
unnamed: Q1101.3 (D), U1101.4 (K)
unnamed: Q1201.3 (D), U1201.4 (K)
unnamed: Q1401.3 (D), U1401.4 (K)
unnamed: Q1501.3 (D), U1501.4 (K)
unnamed: Q1601.3 (D), U1601.4 (K)
unnamed: Q1701.3 (D), U1701.4 (K)
unnamed: Q1901.3 (D), U1901.4 (K)
unnamed: Q2001.3 (D), U2001.4 (K)
unnamed: Q2101.3 (D), U2101.4 (K)
unnamed: Q2201.3 (D), U2201.4 (K)
unnamed: Q2401.3 (D), U2401.4 (K)
unnamed: Q2501.3 (D), U2501.4 (K)
unnamed: Q2601.3 (D), U2601.4 (K)
unnamed: Q2701.3 (D), U2701.4 (K)
unnamed: Q2901.3 (D), U2901.4 (K)
unnamed: Q3001.3 (D), U3001.4 (K)
unnamed: Q3101.3 (D), U3101.4 (K)
unnamed: Q3201.3 (D), U3201.4 (K)
unnamed: Q3401.3 (D), U3401.4 (K)
unnamed: Q3501.3 (D), U3501.4 (K)
unnamed: Q3601.3 (D), U3601.4 (K)
unnamed: Q3701.3 (D), U3701.4 (K)
unnamed: Q4301.3 (D), U4301.4 (K)
unnamed: Q4401.3 (D), U4401.4 (K)
unnamed: Q4501.3 (D), U4501.4 (K)
unnamed: R104.1, R105.2
unnamed: R105.1, R106.2
unnamed: R12.2, U1.51 (USB_DM)
unnamed: R11.2, U1.52 (USB_DP)
unnamed: C1.1, FB1.2, U6.3 (VIN), U6.5 (EN)
unnamed: R103.1, R106.1, U6.1 (FB)
unnamed: L2.1, U6.4 (SW)
unnamed: R302.2, U301.3 (A)
unnamed: C402.1, U401.8 (DECAP)
unnamed: R502.2, U501.3 (A)
unnamed: R602.2, U601.3 (A)
unnamed: R702.2, U701.3 (A)
unnamed: C802.1, U801.8 (DECAP)
unnamed: R902.2, U901.3 (A)
unnamed: R1002.2, U1001.3 (A)
unnamed: R1102.2, U1101.3 (A)
unnamed: R1202.2, U1201.3 (A)
unnamed: C1302.1, U1301.8 (DECAP)
unnamed: R1402.2, U1401.3 (A)
unnamed: R1502.2, U1501.3 (A)
unnamed: R1602.2, U1601.3 (A)
unnamed: R1702.2, U1701.3 (A)
unnamed: C1802.1, U1801.8 (DECAP)
unnamed: R1902.2, U1901.3 (A)
unnamed: R2002.2, U2001.3 (A)
unnamed: R2102.2, U2101.3 (A)
unnamed: R2202.2, U2201.3 (A)
unnamed: C2302.1, U2301.8 (DECAP)
unnamed: R2402.2, U2401.3 (A)
unnamed: R2502.2, U2501.3 (A)
unnamed: R2602.2, U2601.3 (A)
unnamed: R2702.2, U2701.3 (A)
unnamed: C2802.1, U2801.8 (DECAP)
unnamed: R2902.2, U2901.3 (A)
unnamed: R3002.2, U3001.3 (A)
unnamed: R3102.2, U3101.3 (A)
unnamed: R3202.2, U3201.3 (A)
unnamed: C3302.1, U3301.8 (DECAP)
unnamed: R3402.2, U3401.3 (A)
unnamed: R3502.2, U3501.3 (A)
unnamed: R3602.2, U3601.3 (A)
unnamed: R3702.2, U3701.3 (A)
unnamed: C3802.1, U3801.8 (DECAP)
unnamed: R4302.2, U4301.3 (A)
unnamed: R4402.2, U4401.3 (A)
unnamed: R4502.2, U4501.3 (A)

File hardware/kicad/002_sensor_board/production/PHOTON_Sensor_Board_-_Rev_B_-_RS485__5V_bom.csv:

Designator,Footprint,Quantity,Value,LCSC Part #
C1,0805,1,4.7uF,C1779
"C10, C1301, C1302, C1303, C1801, C1802, C1803, C2301, C2302, C2303, C2801, C2802, C2803, C3301, C3302, C3303, C3801, C3802, C3803, C401, C402, C403, C801, C802, C803",0402,25,1uF,
"C13, C14, C15, C16, C19, C20, C21, C22, C23, C24, C25, C26, C27, C5, C8, C9",0402,16,100nF,
"C1304, C1305, C1306, C1307, C1804, C1805, C1806, C1807, C2304, C2305, C2306, C2307, C2804, C2805, C2806, C2807, C3304, C3305, C3306, C3307, C3804, C3805, C3806, C404, C405, C406, C407, C804, C805, C806, C807",0402,31,1nF,
"C17, C18",0402,2,15pF,
"C2, C3, C6, C7",0402,4,4.7uF,
C4,0805,1,22uF,C45783
CR1,SOD-323_L1.8-W1.3-LS2.5-RD,1,PTVSHC3D7VU,C20615807
D3,0603,1,LED RED,C2286
FB1,0603,1,FerriteBead,C14709
"J1, J2",JST_SH_SM04B-SRSS-TB_1x04-1MP_P1.00mm_Horizontal,2,JST_SH,C160404
J3,USB_C_Receptacle_HRO_TYPE-C-31-M-12,1,USB_C_Receptacle_USB2.0,C165948
L1,L_pol_2016,1,3.3uH,C42411119
L2,1008,1,1uH,C2041556
"Q1001, Q1101, Q1201, Q1401, Q1501, Q1601, Q1701, Q1901, Q2001, Q2101, Q2201, Q2401, Q2501, Q2601, Q2701, Q2901, Q3001, Q301, Q3101, Q3201, Q3401, Q3501, Q3601, Q3701, Q4301, Q4401, Q4501, Q501, Q601, Q701, Q901",SOT-23,31,AO3400A,C20917
R1,0402,1,0Ω,
"R1001, R103, R1101, R1201, R1401, R1501, R1601, R1701, R1901, R2001, R2101, R2201, R2401, R2501, R2601, R2701, R2901, R3001, R301, R3101, R3201, R3401, R3501, R3601, R3701, R4301, R4401, R4501, R501, R601, R701, R901",0402,32,100kΩ,
"R1002, R1102, R1202, R1402, R1502, R1602, R1702, R1902, R2002, R2102, R2202, R2402, R2502, R2602, R2702, R2902, R3002, R302, R3102, R3202, R3402, R3502, R3602, R3702, R4302, R4402, R4502, R502, R602, R702, R902",0402,31,68Ω,
"R1003, R1103, R1203, R1403, R1503, R1603, R1703, R1903, R2003, R2103, R2203, R2403, R2503, R2603, R2703, R2903, R3003, R303, R3103, R3203, R3403, R3503, R3603, R3703, R4303, R4403, R4503, R503, R603, R703, R903",0402,31,4.7kΩ,
"R102, R8",0402,2,10kΩ,
"R104, R105",0402,2,200kΩ,
R106,0402,1,51kΩ,
"R11, R12, R6",0402,3,33Ω,
"R13, R14, R19, R20",0402,4,22Ω,
"R18, R7",0402,2,1kΩ,
"R2, R3",0402,2,5.1kΩ,C25905
"R4, R5",0402,2,120Ω,
U1,RP2350-QFN-60-1EP_7x7_P0.4mm_EP3.4x3.4mm_ThermalVias,1,RP2354_60QFN,C41378174
"U1001, U1101, U1201, U1401, U1501, U1601, U1701, U1901, U2001, U2101, U2201, U2401, U2501, U2601, U2701, U2901, U3001, U301, U3101, U3201, U3401, U3501, U3601, U3701, U4301, U4401, U4501, U501, U601, U701, U901",VCNT2025X01_VIS,31,VCNT2025X01,C7431257
"U1301, U1801, U2301, U2801, U3301, U3801, U401, U801",WQFN16_RTE_TEX,8,TLA2518IRTER,C1855741
U4,DQA0010A,1,TPD4E05U06DQAR,C138714
U5,QFN_24RGTR_TEX,1,THVD1424RGTR,C5359161
U6,SOT-563_DRL0006A,1,TPS62A0569ADRLR,C53151500
Y1,Crystal_SMD_3225-4Pin_3.2x2.5mm,1,ABM8-272-T3,C20625731

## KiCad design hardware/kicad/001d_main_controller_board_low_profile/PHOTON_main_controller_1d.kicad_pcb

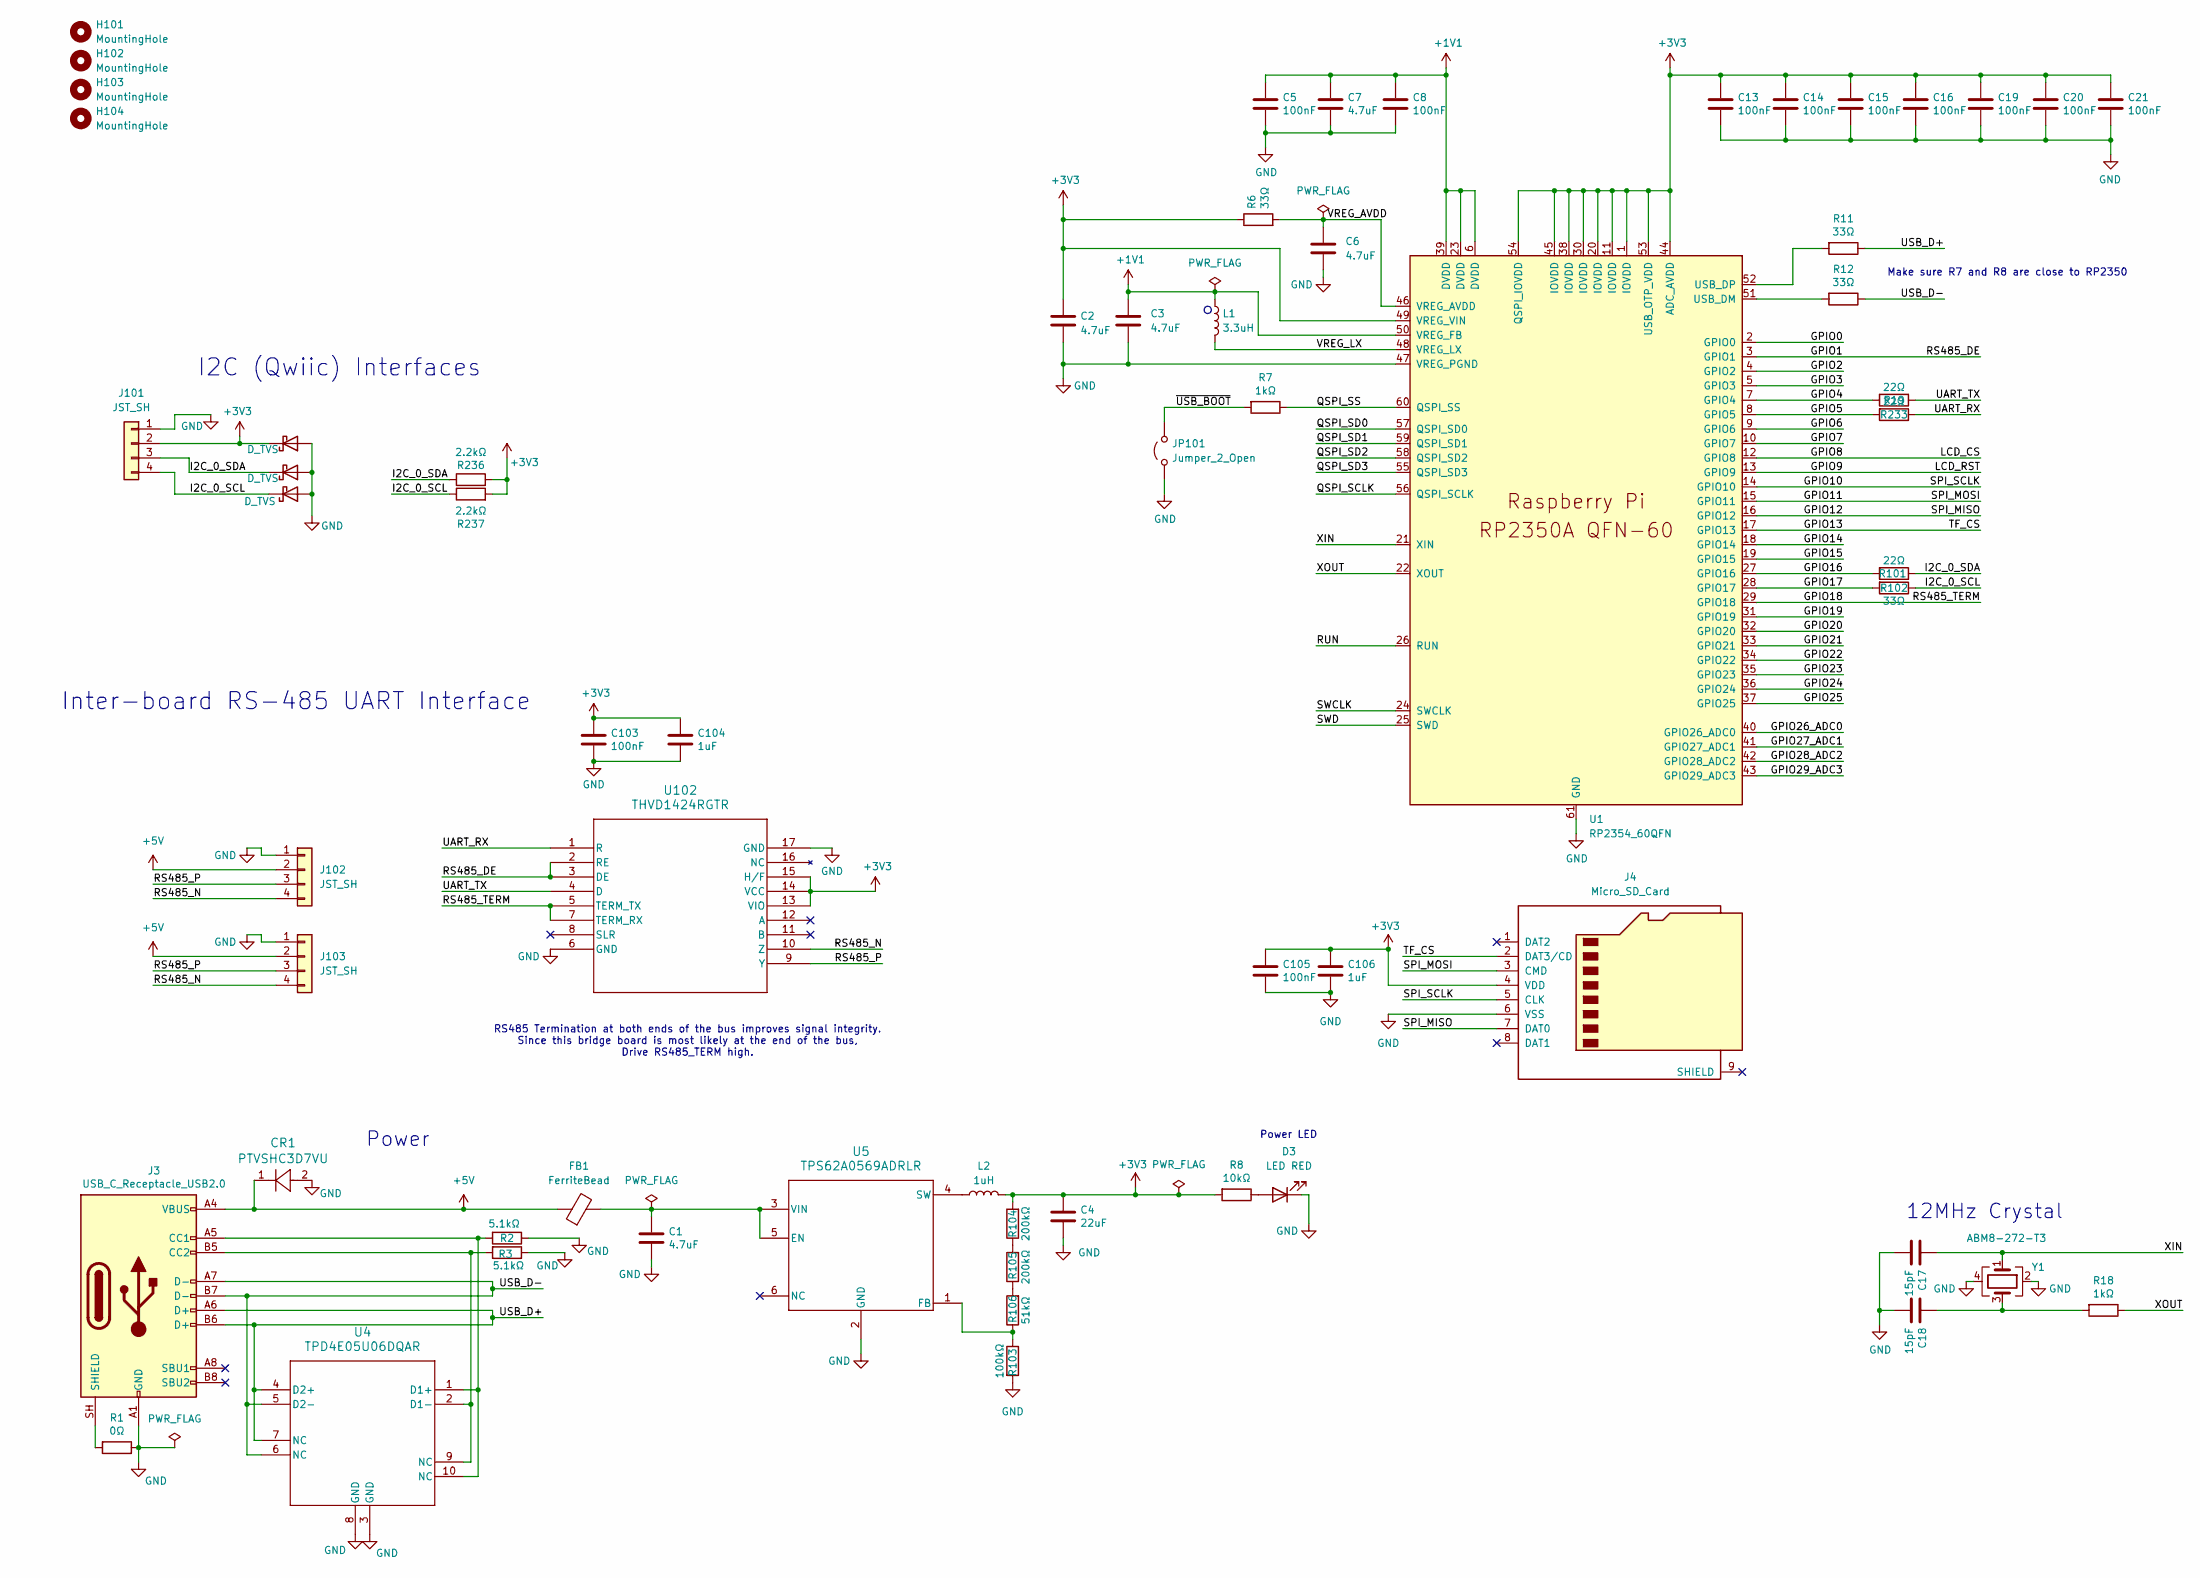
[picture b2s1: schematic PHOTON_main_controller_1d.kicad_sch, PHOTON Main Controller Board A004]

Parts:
C1: 4.7uF; C_0805_2012Metric; Part # CL21A475KAQNNNE; JLCPCB Part # C1779
C2, C3: 4.7uF; C_0402_1005Metric_small_pads
C4: 22uF; C_0805_2012Metric; JLCPCB Part # C45783
C5, C8, C13, C14, C15, C16, C19, C20, C21, C103, C105: 100nF; C_0402_1005Metric; JLCPCB Part # C1525
C6, C7: 4.7uF; C_0402_1005Metric
C17, C18: 15pF; C_0402_1005Metric; JLCPCB Part # C1548
C104, C106: 1uF; C_0402_1005Metric; JLCPCB Part # C52923
CR1: PTVSHC3D7VU; SOD-323_L1.8-W1.3-LS2.5-RD; JLCPCB Part # C20615807
D3: LED RED; LED_0603_1608Metric; JLCPCB Part # C2286
D10, D11, D12: D_TVS; D_SOD-523; JLCPCB Part # C20617921
FB1: FerriteBead; L_0603_1608Metric; JLCPCB Part # C14709
H101, H102, H103, H104: MountingHole; MountingHole_2.7mm_M2.5_Keepout
J3: USB_C_Receptacle_USB2.0; USB_C_Receptacle_HRO_TYPE-C-31-M-12; MPN TYPE-C-31-M-12; JLCPCB Part # C165948
J4: Micro_SD_Card; TF-015_corrected; JLCPCB Part # C113206
J101, J102, J103: JST_SH; JST_SH_SM04B-SRSS-TB_1x04-1MP_P1.00mm_Horizontal; Part Number SM04B-SRSS-TB(LF)(SN); JLCPCB Part # C160404
JP101: Jumper_2_Open; SolderJumper-2_P1.3mm_Open_Pad1.0x1.5mm
L1: 3.3uH; L_pol_2016; JLCPCB Part # C42411119
L2: 1uH; L_1008_2520Metric; Part # C2041556; JLCPCB Part # C2041556
R1: 0Ω; R_0402_1005Metric
R2, R3: 5.1kΩ; R_0402_1005Metric; JLCPCB Part # C25905
R6, R11, R12, R102: 33Ω; R_0402_1005Metric
R7, R18: 1kΩ; R_0402_1005Metric
R8: 10kΩ; R_0402_1005Metric
R19, R101, R233: 22Ω; R_0402_1005Metric
R103: 100kΩ; R_0402_1005Metric
R104, R105: 200kΩ; R_0402_1005Metric
R106: 51kΩ; R_0402_1005Metric
R236, R237: 2.2kΩ; R_0402_1005Metric
U1: RP2354_60QFN; RP2350-QFN-60-1EP_7x7_P0.4mm_EP3.4x3.4mm_ThermalVias; JLCPCB Part # C41378174
U4: TPD4E05U06DQAR; DQA0010A; JLCPCB Part # C138714
U5: TPS62A0569ADRLR; SOT-563_DRL0006A; JLCPCB Part # C53151500
U102: THVD1424RGTR; QFN_24RGTR_TEX; JLCPCB Part # C5359161
Y1: ABM8-272-T3; Crystal_SMD_3225-4Pin_3.2x2.5mm; JLCPCB Part # C20625731

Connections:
+1V1: C3.1, C5.1, C7.1, C8.1, L1.1, U1.6 (DVDD), U1.23 (DVDD), U1.39 (DVDD), U1.50 (VREG_FB)
+3V3: C2.1, C4.1, C13.1, C14.1, C15.1, C16.1, C19.1, C20.1, C21.1, C103.1, C104.1, C105.1, C106.1, D12.1 (K), J4.4 (VDD), J101.2, L2.2, R6.1, R8.2, R104.2, R236.2, R237.2, U1.1 (IOVDD), U1.11 (IOVDD), U1.20 (IOVDD), U1.30 (IOVDD), U1.38 (IOVDD), U1.44 (ADC_AVDD), U1.45 (IOVDD), U1.49 (VREG_VIN), U1.53 (USB_OTP_VDD), U1.54 (QSPI_IOVDD), U102.13 (VIO), U102.14 (VCC), U102.15 (H/F)
+5V: CR1.1, FB1.1, J3.A4 (VBUS), J3.A9 (VBUS), J3.B4 (VBUS), J3.B9 (VBUS), J102.2, J103.2
/GPIO0: U1.2 (GPIO0)
/GPIO1: U1.3 (GPIO1), U102.2 (RE), U102.3 (DE)
/GPIO2: U1.4 (GPIO2)
/GPIO3: U1.5 (GPIO3)
/GPIO4: R19.2, U1.7 (GPIO4)
/GPIO5: R233.2, U1.8 (GPIO5)
/GPIO6: U1.9 (GPIO6)
/GPIO7: U1.10 (GPIO7)
/GPIO8: U1.12 (GPIO8)
/GPIO9: U1.13 (GPIO9)
/GPIO10: J4.5 (CLK), U1.14 (GPIO10)
/GPIO11: J4.3 (CMD), U1.15 (GPIO11)
/GPIO12: J4.7 (DAT0), U1.16 (GPIO12)
/GPIO13: J4.2 (DAT3/CD), U1.17 (GPIO13)
/GPIO14: U1.18 (GPIO14)
/GPIO15: U1.19 (GPIO15)
/GPIO16: R101.2, U1.27 (GPIO16)
/GPIO17: R102.2, U1.28 (GPIO17)
/GPIO18: U1.29 (GPIO18), U102.5 (TERM_TX), U102.7 (TERM_RX)
/GPIO19: U1.31 (GPIO19)
/GPIO20: U1.32 (GPIO20)
/GPIO21: U1.33 (GPIO21)
/GPIO22: U1.34 (GPIO22)
/GPIO23: U1.35 (GPIO23)
/GPIO24: U1.36 (GPIO24)
/GPIO25: U1.37 (GPIO25)
/GPIO26_ADC0: U1.40 (GPIO26_ADC0)
/GPIO27_ADC1: U1.41 (GPIO27_ADC1)
/GPIO28_ADC2: U1.42 (GPIO28_ADC2)
/GPIO29_ADC3: U1.43 (GPIO29_ADC3)
/I2C_0_SCL: D11.1 (K), J101.4, R102.1, R237.1
/I2C_0_SDA: D10.1 (K), J101.3, R101.1, R236.1
/QSPI_SCLK: U1.56 (QSPI_SCLK)
/QSPI_SD0: U1.57 (QSPI_SD0)
/QSPI_SD1: U1.59 (QSPI_SD1)
/QSPI_SD2: U1.58 (QSPI_SD2)
/QSPI_SD3: U1.55 (QSPI_SD3)
/QSPI_SS: R7.1, U1.60 (QSPI_SS)
/RS485_N: J102.4, J103.4, U102.10 (Z)
/RS485_P: J102.3, J103.3, U102.9 (Y)
/RUN: U1.26 (RUN)
/SWCLK: U1.24 (SWCLK)
/SWD: U1.25 (SWD)
/UART_RX: R233.1, U102.1 (R)
/UART_TX: R19.1, U102.4 (D)
/USB_D+: J3.A6 (D+), J3.B6 (D+), R11.1, U4.4 (D2+), U4.7 (NC)
/USB_D-: J3.A7 (D-), J3.B7 (D-), R12.1, U4.5 (D2-), U4.6 (NC)
/VREG_AVDD: C6.1, R6.2, U1.46 (VREG_AVDD)
/VREG_LX: L1.2, U1.48 (VREG_LX)
/XIN: C17.1, U1.21 (XIN), Y1.1
/XOUT: R18.1, U1.22 (XOUT)
/~USB_BOOT: JP101.2 (B), R7.2
GND: C1.2, C2.2, C3.2, C4.2, C5.2, C6.2, C7.2, C8.2, C13.2, C14.2, C15.2, C16.2, C17.2, C18.2, C19.2, C20.2, C21.2, C103.2, C104.2, C105.2, C106.2, CR1.2, D3.1 (K), D10.2 (A), D11.2 (A), D12.2 (A), J3.A1 (GND), J3.A12 (GND), J3.B1 (GND), J3.B12 (GND), J4.6 (VSS), J101.1, J102.1, J103.1, JP101.1 (A), R1.1, R2.1, R3.1, R103.2, U1.47 (VREG_PGND), U1.61 (GND), U4.3 (GND), U4.8 (GND), U5.2 (GND), U102.6 (GND), U102.17 (GND), Y1.2, Y1.4
unnamed: C18.1, R18.2, Y1.3
unnamed: D3.2 (A), R8.1
unnamed: J3.A5 (CC1), R2.2, U4.1 (D1+), U4.10 (NC)
unnamed: J3.B5 (CC2), R3.2, U4.2 (D1-), U4.9 (NC)
unnamed: J3.SH (SHIELD), R1.2
unnamed: R104.1, R105.2
unnamed: R105.1, R106.2
unnamed: R12.2, U1.51 (USB_DM)
unnamed: R11.2, U1.52 (USB_DP)
unnamed: C1.1, FB1.2, U5.3 (VIN), U5.5 (EN)
unnamed: R103.1, R106.1, U5.1 (FB)
unnamed: L2.1, U5.4 (SW)

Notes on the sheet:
Inter-board RS-485 UART Interface
Power
12MHz Crystal
I2C (Qwiic) Interfaces
RS485 Termination at both ends of the bus improves signal integrity. Since this bridge board is most likely at the end of the bus, Drive RS485_TERM high.
Power LED
Make sure R7 and R8 are close to RP2350

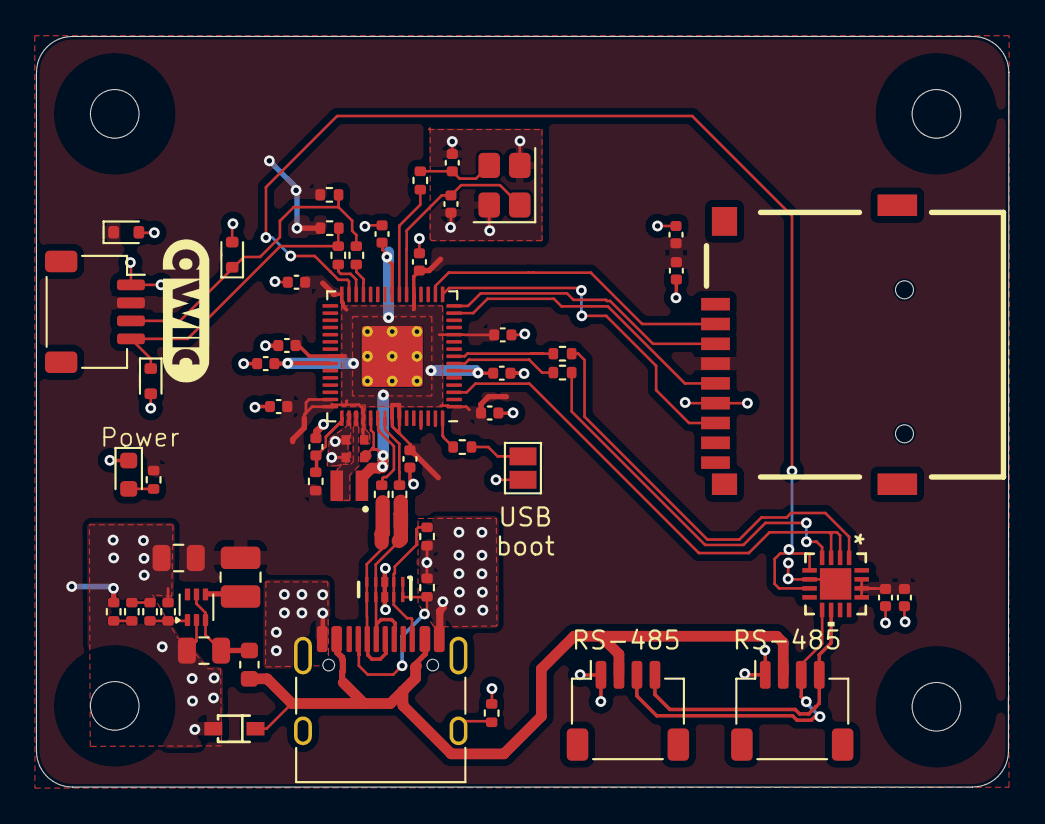
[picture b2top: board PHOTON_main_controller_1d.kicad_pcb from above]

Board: 2 copper layers, 54.0 x 41.7 mm, 63 parts (0 on the bottom side), 40 nets.

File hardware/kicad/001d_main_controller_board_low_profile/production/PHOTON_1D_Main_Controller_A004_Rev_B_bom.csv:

Designator,Footprint,Quantity,Value,LCSC Part #
C1,0805,1,4.7uF,C1779
"C103, C105, C13, C14, C15, C16, C19, C20, C21, C5, C8",0402,11,100nF,C1525
"C104, C106",0402,2,1uF,C52923
"C17, C18",0402,2,15pF,C1548
"C2, C3, C6, C7",0402,4,4.7uF,
C4,0805,1,22uF,C45783
CR1,SOD-323_L1.8-W1.3-LS2.5-RD,1,PTVSHC3D7VU,C20615807
"D10, D11, D12",D_SOD-523,3,D_TVS,C20617921
D3,0603,1,LED RED,C2286
FB1,0603,1,FerriteBead,C14709
"J101, J102, J103",JST_SH_SM04B-SRSS-TB_1x04-1MP_P1.00mm_Horizontal,3,JST_SH,C160404
J3,USB_C_Receptacle_HRO_TYPE-C-31-M-12,1,USB_C_Receptacle_USB2.0,C165948
J4,TF-015_corrected,1,Micro_SD_Card,C113206
L1,L_pol_2016,1,3.3uH,C42411119
L2,1008,1,1uH,C2041556
R1,0402,1,0Ω,
"R101, R19, R233",0402,3,22Ω,
"R102, R11, R12, R6",0402,4,33Ω,
R103,0402,1,100kΩ,
"R104, R105",0402,2,200kΩ,
R106,0402,1,51kΩ,
"R18, R7",0402,2,1kΩ,
"R2, R3",0402,2,5.1kΩ,C25905
"R236, R237",0402,2,2.2kΩ,
R8,0402,1,10kΩ,
U1,RP2350-QFN-60-1EP_7x7_P0.4mm_EP3.4x3.4mm_ThermalVias,1,RP2354_60QFN,C41378174
U102,QFN_24RGTR_TEX,1,THVD1424RGTR,C5359161
U4,DQA0010A,1,TPD4E05U06DQAR,C138714
U5,SOT-563_DRL0006A,1,TPS62A0569ADRLR,C53151500
Y1,Crystal_SMD_3225-4Pin_3.2x2.5mm,1,ABM8-272-T3,C20625731
